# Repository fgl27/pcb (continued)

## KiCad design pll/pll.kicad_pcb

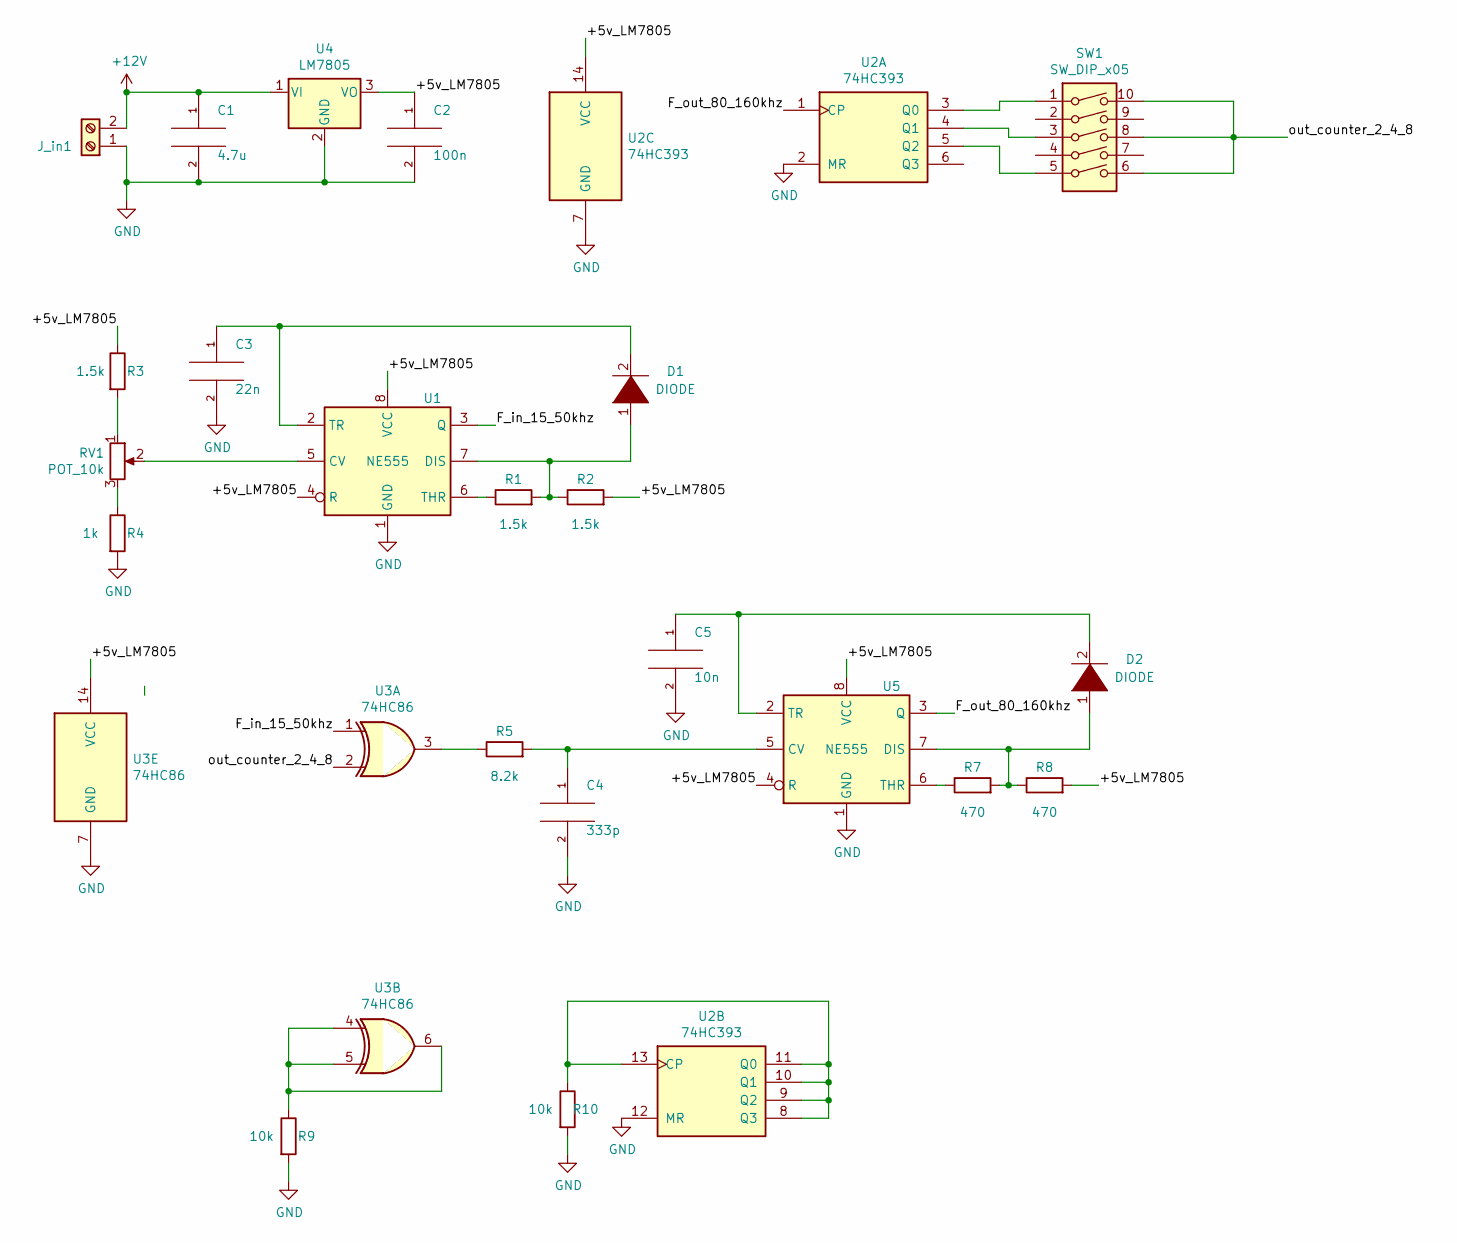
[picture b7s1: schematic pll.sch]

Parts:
C1: 4.7u; CP_Radial_D5.0mm_P2.50mm
C2: 100n; C_Disc_D7.5mm_W5.0mm_P5.00mm
C3: 22n; C_Disc_D7.5mm_W5.0mm_P5.00mm
C4: 333p; C_Disc_D7.5mm_W5.0mm_P5.00mm
C5: 10n; C_Disc_D7.5mm_W5.0mm_P5.00mm
D1, D2: DIODE; D_DO-41_SOD81_P12.70mm_Horizontal
J_in1: Screw_Terminal_01x02; BarrelJack_Horizontal
R1, R2, R3: 1.5k; R_Axial_DIN0207_L6.3mm_D2.5mm_P10.16mm_Horizontal
R4: 1k; R_Axial_DIN0207_L6.3mm_D2.5mm_P10.16mm_Horizontal
R5: 8.2k; R_Axial_DIN0207_L6.3mm_D2.5mm_P10.16mm_Horizontal
R7, R8: 470; R_Axial_DIN0207_L6.3mm_D2.5mm_P10.16mm_Horizontal
R9, R10: 10k; R_Axial_DIN0207_L6.3mm_D2.5mm_P10.16mm_Horizontal
RV1: POT_10k; Potentiometer_Alps_RK163_Single_Horizontal
SW1: SW_DIP_x05; DIP-10_W7.62mm_LongPads
U1, U5: NE555; DIP-8_W7.62mm_LongPads
U2: 74HC393; DIP-14_W7.62mm_LongPads
U3: 74HC86; DIP-14_W7.62mm_LongPads
U4: LM7805; TO-220-3_Vertical

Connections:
+12V: C1.1, J_in1.2, U4.1 (VI)
/+5v_LM7805: C2.1, R2.2, R3.1, R8.2, U1.4 (R), U1.8 (VCC), U2.14 (VCC), U3.14 (VCC), U4.3 (VO), U5.4 (R), U5.8 (VCC)
/F_in_15_50khz: U1.3 (Q), U3.1
/F_out_80_160khz: U2.1 (CP), U5.3 (Q)
/out_counter_2_4_8: SW1.6, SW1.8, SW1.10, U3.2
GND: C1.2, C2.2, C3.2, C4.2, C5.2, J_in1.1, R4.2, R9.2, R10.2, U1.1 (GND), U2.2 (MR), U2.7 (GND), U2.12 (MR), U3.7 (GND), U4.2 (GND), U5.1 (GND)
unnamed: C3.1, D1.2 (A), U1.2 (TR)
unnamed: C4.1, R5.2, U5.5 (CV)
unnamed: C5.1, D2.2 (A), U5.2 (TR)
unnamed: D1.1 (K), R1.2, R2.1, U1.7 (DIS)
unnamed: D2.1 (K), R7.2, R8.1, U5.7 (DIS)
unnamed: R1.1, U1.6 (THR)
unnamed: R3.2, RV1.1
unnamed: R4.1, RV1.3
unnamed: R5.1, U3.3
unnamed: R7.1, U5.6 (THR)
unnamed: R9.1, U3.4, U3.5, U3.6
unnamed: R10.1, U2.8 (Q3), U2.9 (Q2), U2.10 (Q1), U2.11 (Q0), U2.13 (CP)
unnamed: RV1.2, U1.5 (CV)
unnamed: SW1.1, U2.3 (Q0)
unnamed: SW1.3, U2.4 (Q1)
unnamed: SW1.5, U2.5 (Q2)

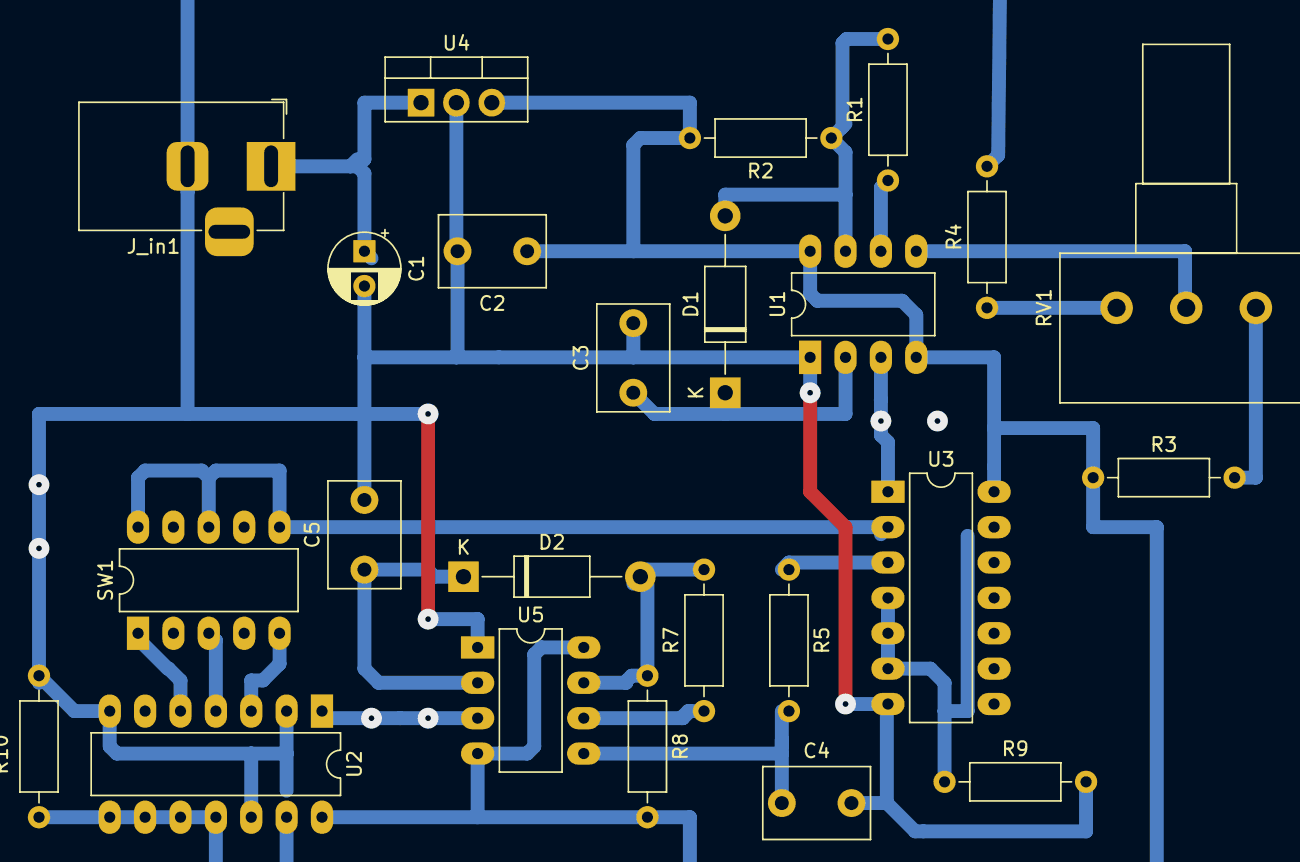
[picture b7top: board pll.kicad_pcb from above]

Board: 2 copper layers, 24 parts (0 on the bottom side), 22 nets.

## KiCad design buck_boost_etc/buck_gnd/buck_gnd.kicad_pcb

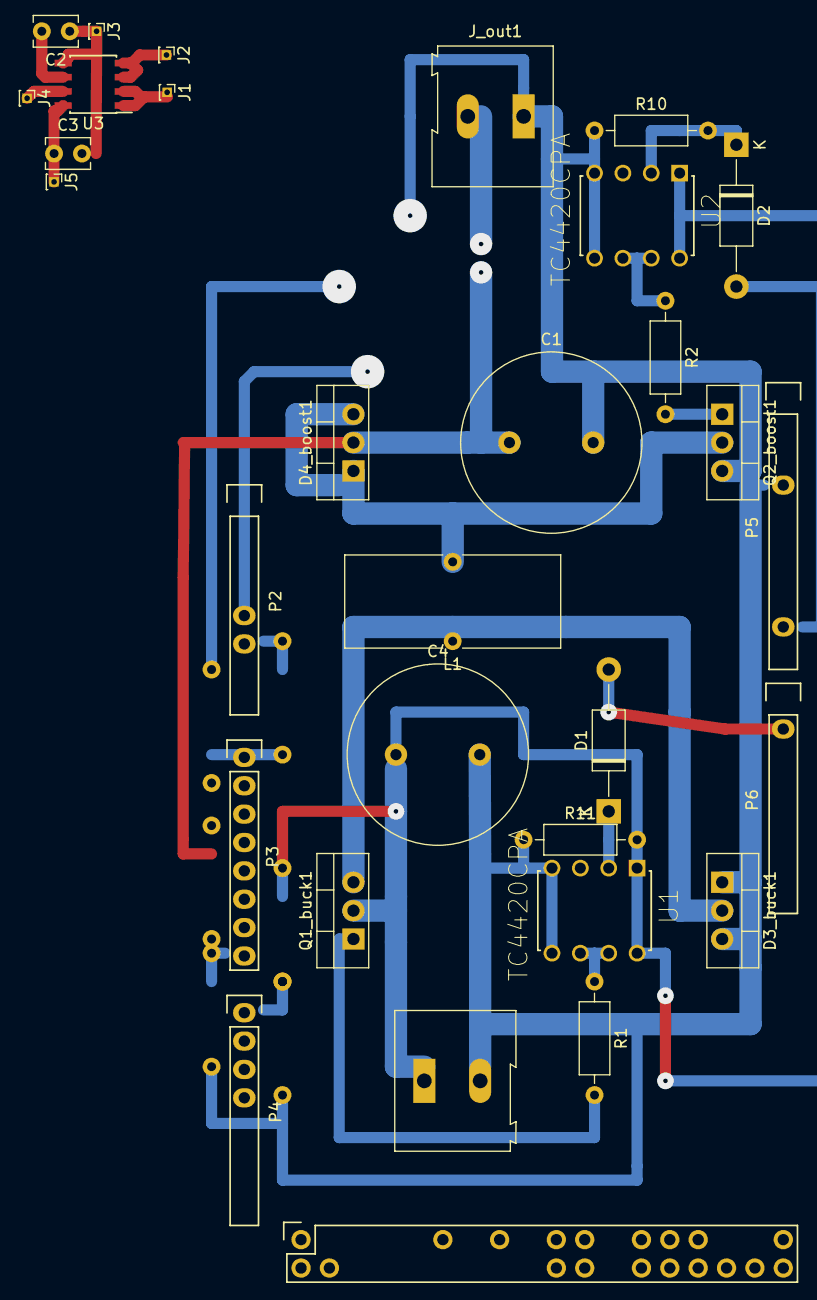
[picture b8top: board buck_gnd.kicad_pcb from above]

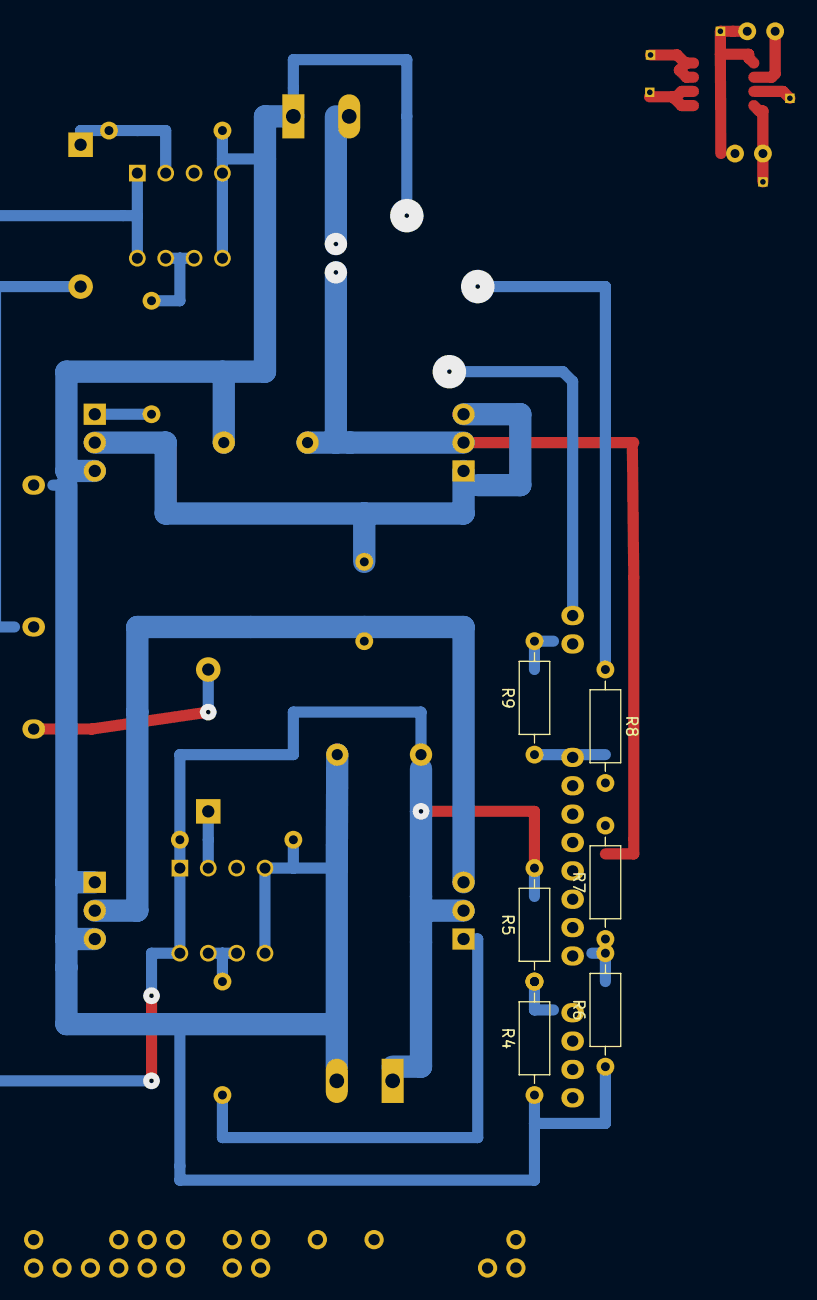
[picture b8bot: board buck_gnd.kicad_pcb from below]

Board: 2 copper layers, 37 parts (6 on the bottom side), 20 nets.

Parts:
ARDUINO DIGITAL I/O: Digital; Socket_Strip_Arduino_2x18
C1, C4: 2200u; C_Radial_D16.0mm_H25.0mm_P7.50mm
C2: 1n; C_Disc_D3.8mm_W2.6mm_P2.50mm
C3: 0.1u; C_Disc_D3.8mm_W2.6mm_P2.50mm
D1, D2: DIODE; D_DO-41_SOD81_P12.70mm_Horizontal
D3_buck1, D4_boost1: D_Schottky_AKA; TO-220-3_Vertical
J1, J2, J3, J4, J5: Conn_01x01_Male; PinHeader_1x01_P1.00mm_Vertical
J_in1: Screw_Terminal_01x02; TerminalBlock_Altech_AK300-2_P5.00mm
J_out1: Screw_Terminal_01x02; TerminalBlock_Altech_AK300-2_P5.00mm
L1: INDUCTOR; L_Toroid_Vertical_L19.1mm_W8.1mm_P7.10mm_Bourns_5700
P2: Power; Socket_Strip_Arduino_1x08
P3, P4: Analog; Socket_Strip_Arduino_1x08
P5: PWM; Socket_Strip_Arduino_1x10
P6: PWM; Socket_Strip_Arduino_1x08
Q1_buck1, Q2_boost1: IRLZ44N; TO-220-3_Vertical
R1, R2: 47R; R_Axial_DIN0207_L6.3mm_D2.5mm_P10.16mm_Horizontal
R4, R6, R8, R9, R10, R11: 10K; R_Axial_DIN0207_L6.3mm_D2.5mm_P10.16mm_Horizontal
R5, R7: 100K; R_Axial_DIN0207_L6.3mm_D2.5mm_P10.16mm_Horizontal
U1, U2: TC4420CPA; DIP254P762X533-8
U3: ACS730xLCTR-50AB; SOIC-8_3.9x4.9mm_P1.27mm

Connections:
+5V: C3.1, J5.1, U3.8
+12V: C4.1, D3_buck1.2, J_in1.1, L1.1, R5.2, U1.1, U1.8, U2.1, U2.8
ADC_Current: J4.1, U3.7
ADC_VIN: R4.2, R5.1
ADC_VOUT: R6.2, R7.1
GND: C4.2, J_in1.2, Q1_buck1.3, R4.1, R6.1, R10.1, R11.1, U1.4, U1.5, U2.4, U2.5
GNDREF: C2.1, C3.2, J3.1, U3.5
unnamed: C1.1, D4_boost1.2, J_out1.2, R7.2
unnamed: C1.2, D3_buck1.1, D3_buck1.3, J_out1.1, Q1_buck1.2, Q2_boost1.3
unnamed: C2.2, U3.6
unnamed: D1.2, R11.2, U1.2
unnamed: D2.2, R10.2, U2.2
unnamed: D4_boost1.1, D4_boost1.3, L1.2, Q2_boost1.2
unnamed: J1.1, U3.1, U3.2
unnamed: J2.1, U3.3, U3.4
unnamed: Q1_buck1.1, R1.2
unnamed: Q2_boost1.1, R2.2
unnamed: R1.1, U1.6, U1.7
unnamed: R2.1, U2.6, U2.7
unnamed: R8.2, R9.1

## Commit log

2019-06-22 Init commit
2019-06-22 Update pll
2021-08-29 Update pcbs
2021-09-05 up pcb
2021-09-06 Up pcbs
2021-09-08 Up ocb
2021-09-11 UP ocbs
2021-11-28 up changes
